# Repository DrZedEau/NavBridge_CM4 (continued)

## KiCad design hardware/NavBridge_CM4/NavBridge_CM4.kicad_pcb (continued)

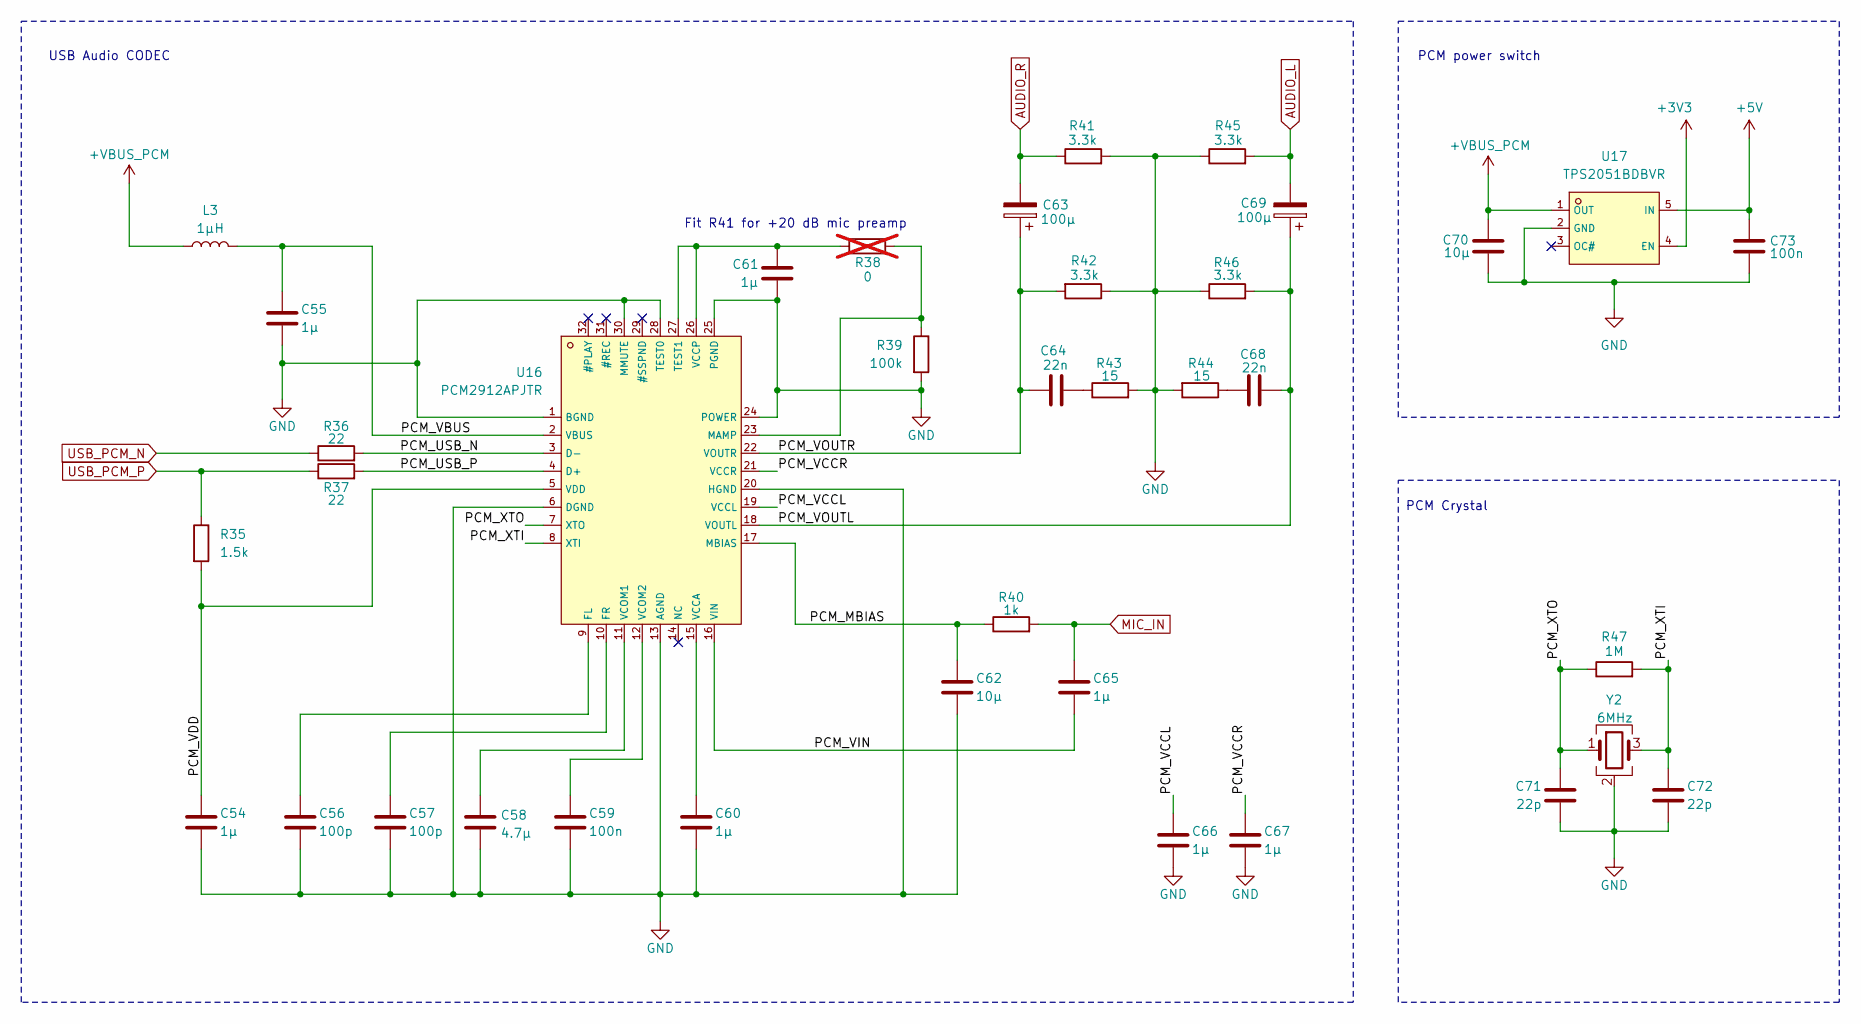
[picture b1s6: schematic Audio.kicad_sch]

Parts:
C54, C55, C60, C61, C65, C66, C67: 1µ; C_0402_1005Metric; LCSC C52923
C56, C57: 100p; C_0402_1005Metric; LCSC C1546
C58: 4.7µ; C_0402_1005Metric; LCSC C23733
C59, C73: 100n; C_0402_1005Metric; LCSC C307331
C62: 10µ; C_0603_1608Metric; LCSC C96446
C63, C69: 100µ; CP_EIA-3528-21_Kemet-B; LCSC C16133
C64, C68: 22n; C_0402_1005Metric; LCSC C1532
C70: 10µ; C_0805_2012Metric; LCSC C15850
C71, C72: 22p; C_0402_1005Metric; LCSC C1555
L3: 1µH; L_1008_2520Metric; LCSC C435392
R35: 1.5k; R_0402_1005Metric; LCSC C25867
R36, R37: 22; R_0402_1005Metric; LCSC C25092
R38: 0; R_0603_1608Metric; LCSC C17168; not fitted
R39: 100k; R_0402_1005Metric; LCSC C25741
R40: 1k; R_0402_1005Metric; LCSC C11702
R41, R42, R45, R46: 3.3k; R_0402_1005Metric; LCSC C25890
R43, R44: 15; R_0603_1608Metric; LCSC C22810
R47: 1M; R_0402_1005Metric; LCSC C26083
U16: PCM2912APJTR; C475497_TQFP-32_L7_0-W7_0-P0_80-LS9_0-TL; LCSC C475497
U17: TPS2051BDBVR; C24593_SOT-23-5_L3_0-W1_7-P0_95-LS2_8-BR; LCSC C24593
Y2: 6MHz; Crystal_SMD_FOX_FQ7050-4Pin_7.0x5.0mm; LCSC C179631

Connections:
+3V3: U17.4 (EN); also elsewhere on the board
+5V: C73.1, U17.5 (IN); also elsewhere on the board
+VBUS_PCM: C70.2, L3.1, U17.1 (OUT)
/Audio/PCM_MBIAS: C62.1, R40.1, U16.17 (MBIAS)
/Audio/PCM_USB_N: R36.2, U16.3 (D-)
/Audio/PCM_USB_P: R37.2, U16.4 (D+)
/Audio/PCM_VBUS: C55.1, L3.2, U16.2 (VBUS)
/Audio/PCM_VCCL: C66.1, U16.19 (VCCL)
/Audio/PCM_VCCR: C67.1, U16.21 (VCCR)
/Audio/PCM_VDD: C54.1, R35.2, U16.5 (VDD)
/Audio/PCM_VIN: C65.2, U16.16 (VIN)
/Audio/PCM_VOUTL: C68.1, C69.1, R46.2, U16.18 (VOUTL)
/Audio/PCM_VOUTR: C63.1, C64.1, R42.2, U16.22 (VOUTR)
/Audio/PCM_XTI: C72.1, R47.2, U16.8 (XTI), Y2.3
/Audio/PCM_XTO: C71.1, R47.1, U16.7 (XTO), Y2.1
AUDIO_L: C69.2, R45.2; also elsewhere on the board
AUDIO_R: C63.2, R41.1; also elsewhere on the board
GND: C54.2, C55.2, C56.2, C57.2, C58.2, C59.2, C60.2, C61.2, C62.2, C66.2, C67.2, C70.1, C71.2, C72.2, C73.2, R39.2, R41.2, R42.1, R43.2, R44.2, R45.1, R46.1, U16.1 (BGND), U16.6 (DGND), U16.13 (AGND), U16.20 (HGND), U16.24 (POWER), U16.25 (PGND), U16.28 (TEST0), U16.30 (MMUTE), U17.2 (GND), Y2.2 (G), Y2.4 (G); also elsewhere on the board
MIC_IN: C65.1, R40.2; also elsewhere on the board
unnamed: C64.2, R43.1
unnamed: C68.2, R44.1
unnamed: C56.1, U16.9 (FL)
unnamed: C57.1, U16.10 (FR)
unnamed: R38.2, R39.1, U16.23 (MAMP)
unnamed: C61.1, R38.1, U16.26 (VCCP), U16.27 (TEST1)
unnamed: C60.1, U16.15 (VCCA)
unnamed: C58.1, U16.11 (VCOM1)
unnamed: C59.1, U16.12 (VCOM2)
USB_PCM_N: R36.1; also elsewhere on the board
USB_PCM_P: R35.1, R37.1; also elsewhere on the board

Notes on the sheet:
PCM Crystal
Fit R41 for +20 dB mic preamp
USB Audio CODEC
PCM power switch

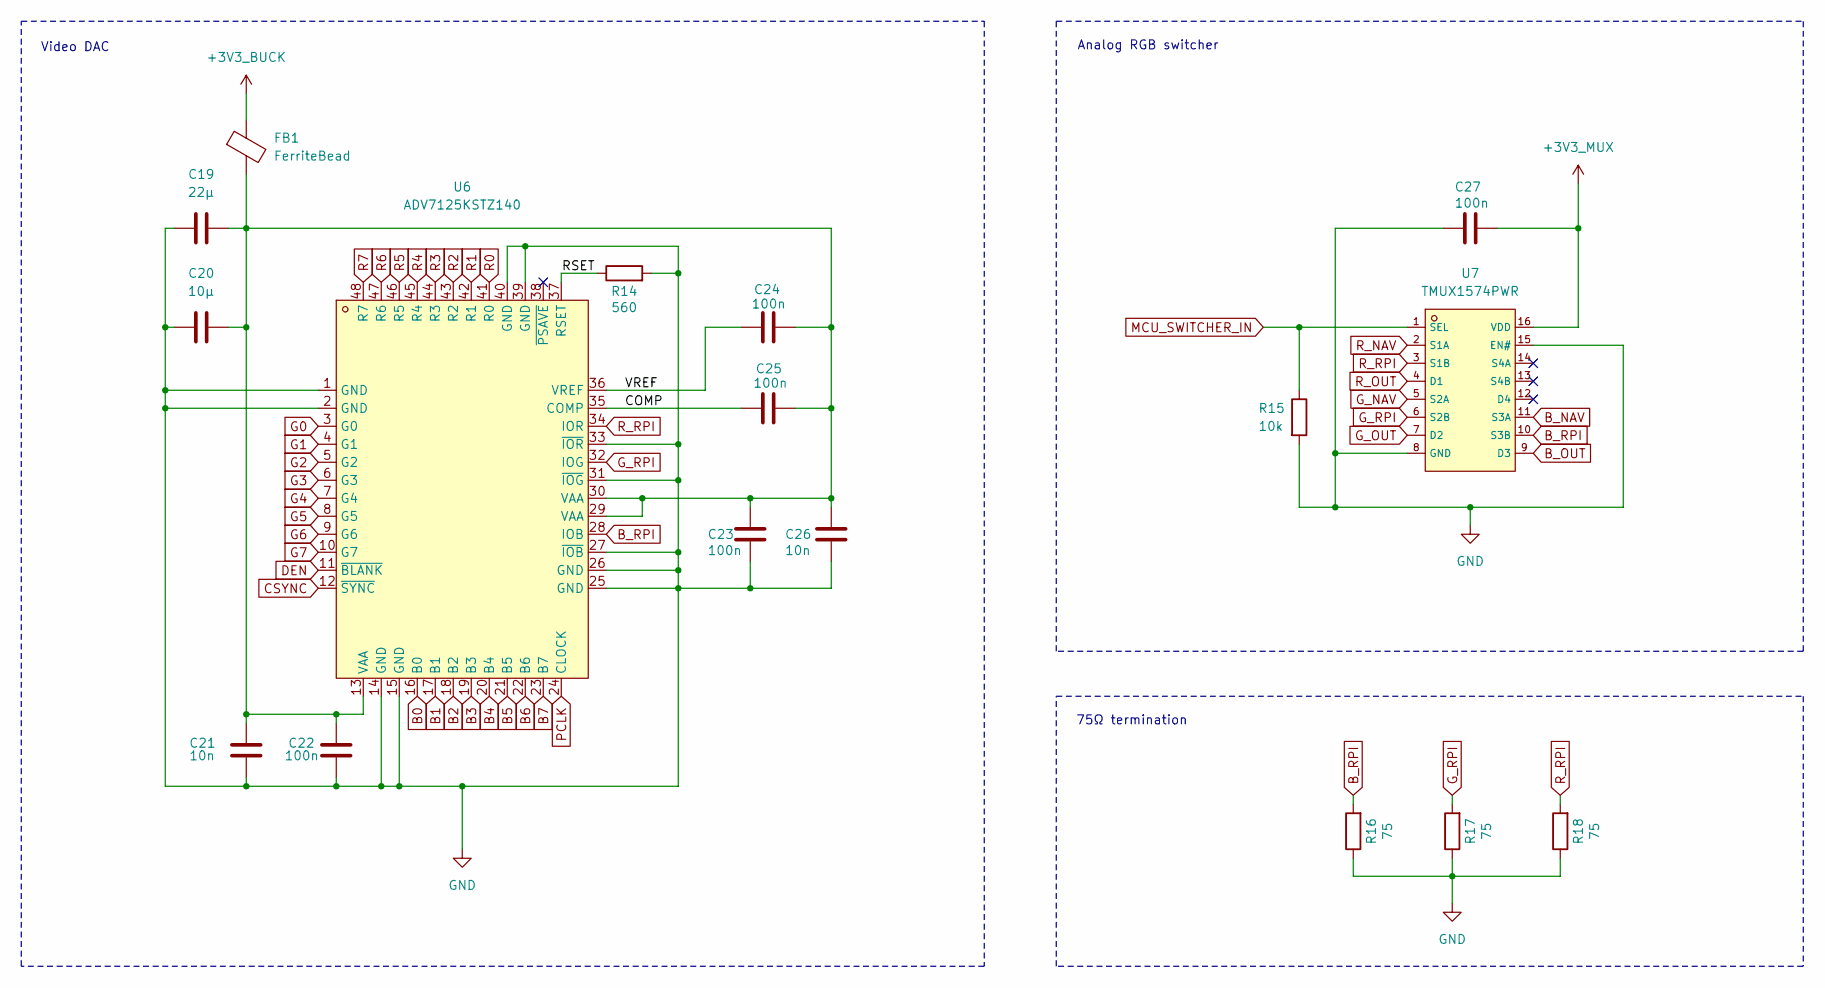
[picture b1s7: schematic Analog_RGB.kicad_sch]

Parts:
C19: 22µ; C_0805_2012Metric; LCSC C45783
C20: 10µ; C_0603_1608Metric; LCSC C19702
C21, C26: 10n; C_0402_1005Metric; LCSC C15195
C22, C23, C24, C25, C27: 100n; C_0402_1005Metric; LCSC C307331
FB1: FerriteBead; R_0603_1608Metric; LCSC C14709
R14: 560; R_0603_1608Metric; LCSC C23204
R15: 10k; R_0402_1005Metric; LCSC C25744
R16, R17, R18: 75; R_0402_1005Metric; LCSC C25133
U6: ADV7125KSTZ140; LQFP-48_L7.0-W7.0-P0.50-LS9.0-BL; LCSC Part C9668
U7: TMUX1574PWR; C2673443_TSSOP-16_L5_0-W4_4-P0_65-LS6_4-BL; LCSC C2673443

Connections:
+3V3_BUCK: FB1.1; also elsewhere on the board
+3V3_MUX: C27.2, U7.16 (VDD); also elsewhere on the board
/Analog_RGB/COMP: C25.2, U6.35 (COMP)
/Analog_RGB/RSET: R14.1, U6.37 (RSET)
/Analog_RGB/VREF: C24.2, U6.36 (VREF)
B0: U6.16 (B0); also elsewhere on the board
B1: U6.17 (B1); also elsewhere on the board
B2: U6.18 (B2); also elsewhere on the board
B3: U6.19 (B3); also elsewhere on the board
B4: U6.20 (B4); also elsewhere on the board
B5: U6.21 (B5); also elsewhere on the board
B6: U6.22 (B6); also elsewhere on the board
B7: U6.23 (B7); also elsewhere on the board
B_NAV: U7.11 (S3A); also elsewhere on the board
B_OUT: U7.9 (D3); also elsewhere on the board
B_RPI: R16.2, U6.28 (IOB), U7.10 (S3B)
CSYNC: U6.12 (~SYNC); also elsewhere on the board
DEN: U6.11 (~BLANK); also elsewhere on the board
G0: U6.3 (G0); also elsewhere on the board
G1: U6.4 (G1); also elsewhere on the board
G2: U6.5 (G2); also elsewhere on the board
G3: U6.6 (G3); also elsewhere on the board
G4: U6.7 (G4); also elsewhere on the board
G5: U6.8 (G5); also elsewhere on the board
G6: U6.9 (G6); also elsewhere on the board
G7: U6.10 (G7); also elsewhere on the board
GND: C19.1, C20.1, C21.1, C22.1, C23.1, C26.1, C27.1, R14.2, R15.2, R16.1, R17.1, R18.1, U6.1 (GND), U6.2 (GND), U6.14 (GND), U6.15 (GND), U6.25 (GND), U6.26 (GND), U6.27 (~IOB), U6.31 (~IOG), U6.33 (~IOR), U6.39 (GND), U6.40 (GND), U7.8 (GND), U7.15 (EN#); also elsewhere on the board
G_NAV: U7.5 (S2A); also elsewhere on the board
G_OUT: U7.7 (D2); also elsewhere on the board
G_RPI: R17.2, U6.32 (IOG), U7.6 (S2B)
MCU_SWITCHER_IN: R15.1, U7.1 (SEL); also elsewhere on the board
unnamed: C19.2, C20.2, C21.2, C22.2, C23.2, C24.1, C25.1, C26.2, FB1.2, U6.13 (VAA), U6.29 (VAA), U6.30 (VAA)
PCLK: U6.24 (CLOCK); also elsewhere on the board
R0: U6.41 (R0); also elsewhere on the board
R1: U6.42 (R1); also elsewhere on the board
R2: U6.43 (R2); also elsewhere on the board
R3: U6.44 (R3); also elsewhere on the board
R4: U6.45 (R4); also elsewhere on the board
R5: U6.46 (R5); also elsewhere on the board
R6: U6.47 (R6); also elsewhere on the board
R7: U6.48 (R7); also elsewhere on the board
R_NAV: U7.2 (S1A); also elsewhere on the board
R_OUT: U7.4 (D1); also elsewhere on the board
R_RPI: R18.2, U6.34 (IOR), U7.3 (S1B)

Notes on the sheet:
Video DAC
Analog RGB switcher
75Ω termination

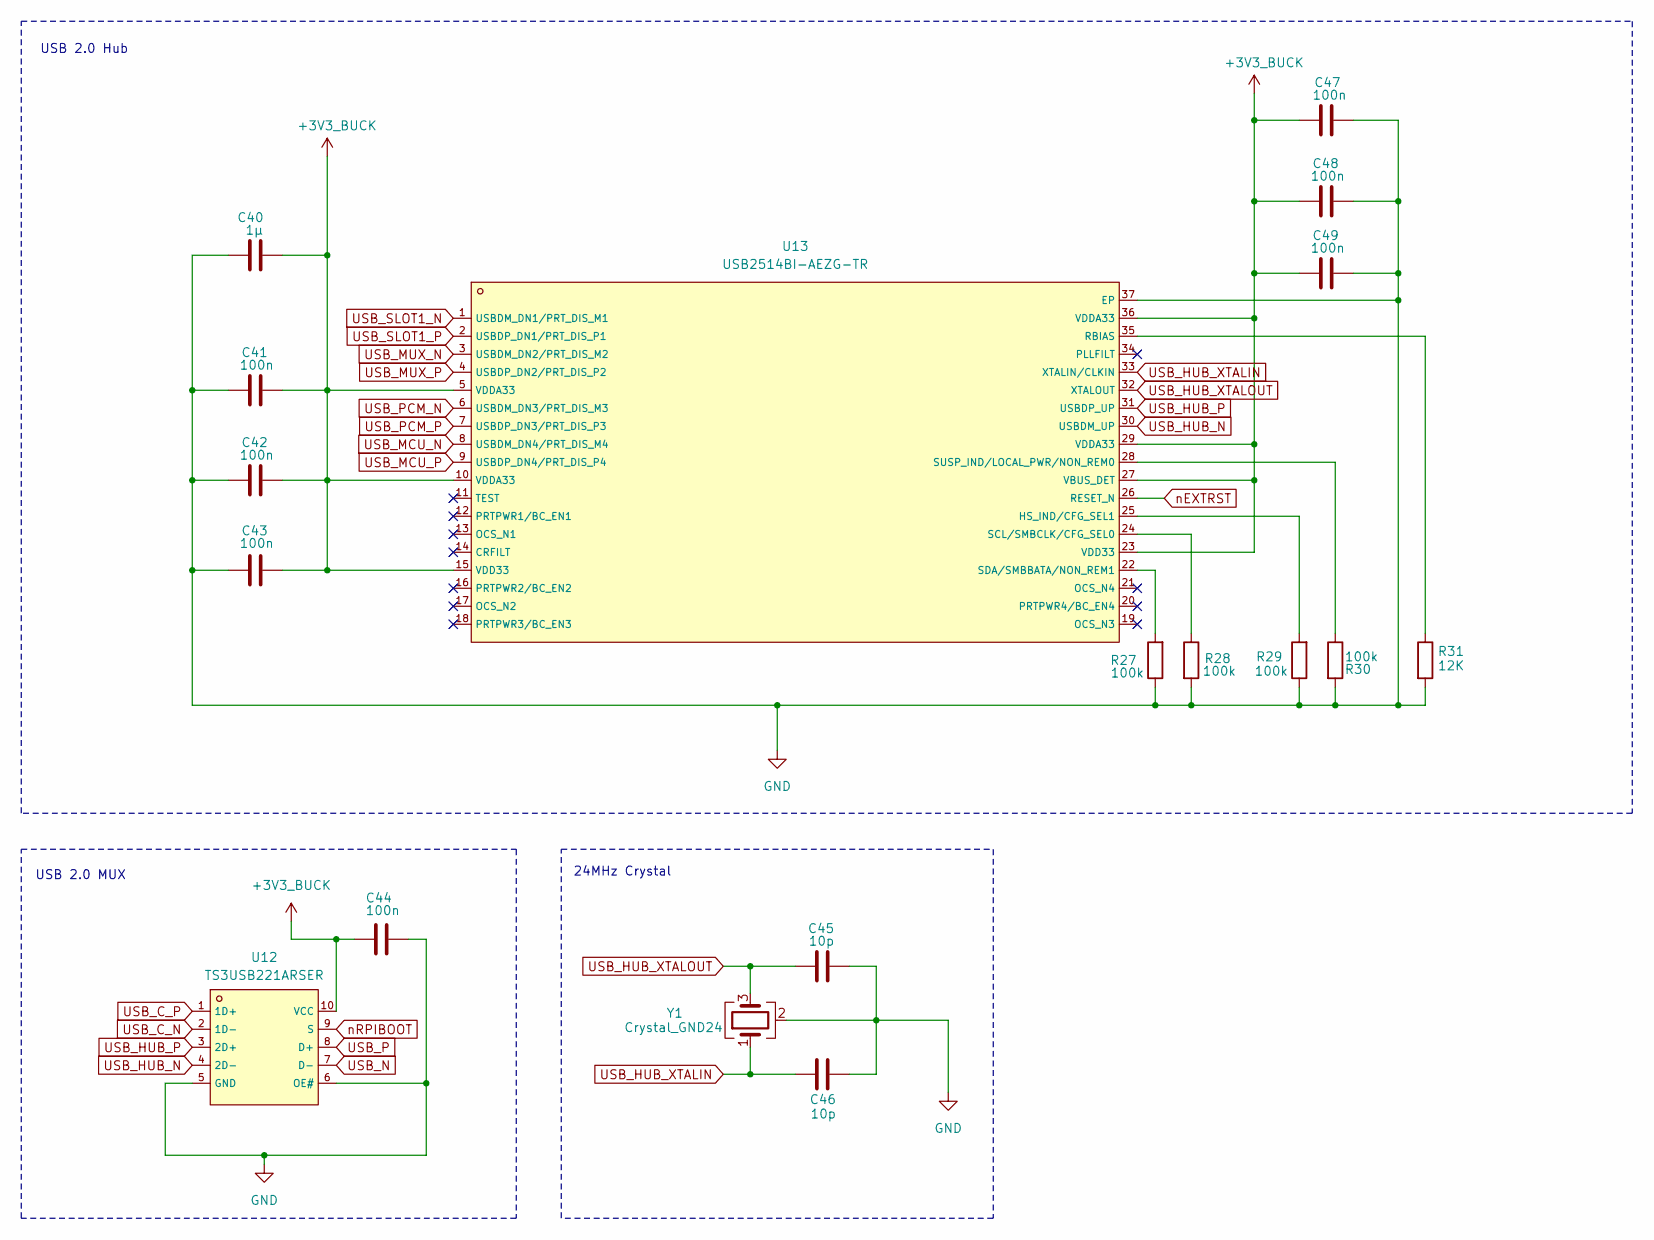
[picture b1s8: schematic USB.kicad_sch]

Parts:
C40: 1µ; C_0402_1005Metric; LCSC C52923
C41, C42, C43, C44, C47, C48, C49: 100n; C_0402_1005Metric; LCSC C307331
C45, C46: 10p; C_0402_1005Metric; LCSC C32949
R27, R28, R29, R30: 100k; R_0402_1005Metric; LCSC C25741
R31: 12K; R_0402_1005Metric; LCSC C25752
U12: TS3USB221ARSER; C128396_UQFN-10_L2_0-W1_5-P0_50-BL; LCSC C128396
U13: USB2514BI-AEZG-TR; C58940_TQFN-36_L6_0-W6_0-P0_50-BL-EP3_7; LCSC C58940
Y1: Crystal_GND24; Crystal_SMD_2016-4Pin_2.0x1.6mm; LCSC C6616880

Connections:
+3V3_BUCK: C40.2, C41.2, C42.2, C43.2, C44.1, C47.1, C48.1, C49.1, U12.10 (VCC), U13.5 (VDDA33), U13.10 (VDDA33), U13.15 (VDD33), U13.23 (VDD33), U13.27 (VBUS_DET), U13.29 (VDDA33), U13.36 (VDDA33); also elsewhere on the board
GND: C40.1, C41.1, C42.1, C43.1, C44.2, C45.2, C46.2, C47.2, C48.2, C49.2, R27.1, R28.2, R29.1, R30.2, R31.2, U12.5 (GND), U12.6 (OE#), U13.37 (EP), Y1.2 (G), Y1.4 (G); also elsewhere on the board
unnamed: R29.2, U13.25 (HS_IND/CFG_SEL1)
unnamed: R31.1, U13.35 (RBIAS)
unnamed: R28.1, U13.24 (SCL/SMBCLK/CFG_SEL0)
unnamed: R27.2, U13.22 (SDA/SMBBATA/NON_REM1)
unnamed: R30.1, U13.28 (SUSP_IND/LOCAL_PWR/NON_REM0)
USB_C_N: U12.2 (1D-); also elsewhere on the board
USB_C_P: U12.1 (1D+); also elsewhere on the board
USB_HUB_N: U12.4 (2D-), U13.30 (USBDM_UP)
USB_HUB_P: U12.3 (2D+), U13.31 (USBDP_UP)
USB_HUB_XTALIN: C46.1, U13.33 (XTALIN/CLKIN), Y1.1
USB_HUB_XTALOUT: C45.1, U13.32 (XTALOUT), Y1.3
USB_MCU_N: U13.8 (USBDM_DN4/PRT_DIS_M4); also elsewhere on the board
USB_MCU_P: U13.9 (USBDP_DN4/PRT_DIS_P4); also elsewhere on the board
USB_MUX_N: U13.3 (USBDM_DN2/PRT_DIS_M2); also elsewhere on the board
USB_MUX_P: U13.4 (USBDP_DN2/PRT_DIS_P2); also elsewhere on the board
USB_N: U12.7 (D-); also elsewhere on the board
USB_P: U12.8 (D+); also elsewhere on the board
USB_PCM_N: U13.6 (USBDM_DN3/PRT_DIS_M3); also elsewhere on the board
USB_PCM_P: U13.7 (USBDP_DN3/PRT_DIS_P3); also elsewhere on the board
USB_SLOT1_N: U13.1 (USBDM_DN1/PRT_DIS_M1); also elsewhere on the board
USB_SLOT1_P: U13.2 (USBDP_DN1/PRT_DIS_P1); also elsewhere on the board
nEXTRST: U13.26 (RESET_N); also elsewhere on the board
nRPIBOOT: U12.9 (S); also elsewhere on the board

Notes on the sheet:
USB 2.0 Hub
24MHz Crystal
USB 2.0 MUX

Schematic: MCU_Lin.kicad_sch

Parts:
C28, C30, C31, C34, C35, C37, C38, C39: 100n; C_0402_1005Metric; LCSC C307331
C29, C36: 4.7µ; C_0402_1005Metric; LCSC C23733
C32: 10µ; C_1206_3216Metric; LCSC C13585
C33: 4.7µ; C_0805_2012Metric; LCSC C1779
CN5: 20021521-00010C1LF; C598547_IDC-SMD_10P-P1_27_X1270WVS-2X05B-6TV01; LCSC C598547
D5, D7: 1N4148W; D_SOD-123; LCSC C81598
D6: LED_Y; LED_0603_1608Metric; LCSC C89811
R19, R23: 10k; R_0402_1005Metric; LCSC C25744
R20, R21, R22: 1k; R_0402_1005Metric; LCSC C11702
R24: 1k; R_1206_3216Metric; LCSC C4410
R25: 150k; R_0402_1005Metric; LCSC C25755
R26: 100k; R_0402_1005Metric; LCSC C25741
SW2, SW3: SW_Push; SW_SPST_TS-1088-xR020; LCSC C720477
U8, U10: ATA663231-GBQW; C5225740_DFN-8_L3_0-W3_0-P0_65-BL-EP-1; LCSC C5225740
U9: STM32C071KBTx; LQFP-32_7x7mm_P0.8mm; LCSC C42116633
U11: TPS2117DRLR; C22399676_SOT-583-8_L2_1-W1_2-P0_50-LS1_6-BL; LCSC Part C22399676

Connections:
+3V3: C39.1, CN5.1, R22.1, SW3.2, U11.6 (VIN2); also elsewhere on the board
+3V3_LIN_REG: C29.1, C30.2, C35.2, R25.1, U8.8 (VCC), U11.3 (VIN1), U11.5 (MODE)
+3V3_MUX: C33.1, C34.1, U9.4 (VDD), U11.2 (VOUT), U11.7 (VOUT); also elsewhere on the board
+3V3_SENSE: R22.2, U9.10 (PA3)
+BATT: D5.2 (A), D7.2 (A); also elsewhere on the board
CSYNC: U9.19 (PA9); also elsewhere on the board
GND: C28.1, C29.2, C30.1, C31.1, C32.2, C33.2, C34.2, C35.1, C36.2, C37.2, C38.1, C39.2, CN5.3, CN5.5, CN5.9, D6.1 (K), R19.2, R23.2, R26.2, SW2.1, U8.5 (GND), U8.9 (EP), U9.5 (VSS), U10.5 (GND), U10.9 (EP), U11.1 (GND); also elsewhere on the board
HSYNC: U9.18 (PA8); also elsewhere on the board
IBUS_CAR: U8.6 (LIN); also elsewhere on the board
IBUS_NAV: R24.1, U10.6 (LIN); also elsewhere on the board
MCU_BUCK_EN: U9.9 (PA2); also elsewhere on the board
MCU_LIN1_EN: R19.1, U8.2 (EN), U9.29 (PB5)
MCU_LIN1_RX: U8.1 (RXD), U9.31 (PB7)
MCU_LIN1_TX: U8.4 (TXD), U9.30 (PB6)
MCU_LIN2_EN: R23.1, U9.28 (PB4), U10.2 (EN)
MCU_LIN2_RX: U9.12 (PA5), U10.1 (RXD)
MCU_LIN2_TX: U9.11 (PA4), U10.4 (TXD)
MCU_SWITCHER_IN: U9.21 (PA10); also elsewhere on the board
NRST: C28.2, CN5.10, SW2.2, U9.6 (PF2)
unnamed: D6.2 (A), R20.2
unnamed: D7.1 (K), R24.2
unnamed: R21.1, SW3.1
unnamed: R20.1, U9.8 (PA1)
unnamed: C36.1, C37.1, U10.8 (VCC)
unnamed: R25.2, R26.1, U11.4 (PR1)
SWCLK: CN5.4, R21.2, U9.25 (PA14)
SWDIO: CN5.2, U9.24 (PA13)
USB_MCU_N: U9.22 (PA11); also elsewhere on the board
USB_MCU_P: U9.23 (PA12); also elsewhere on the board
VS: C31.2, C32.1, C38.2, D5.1 (K), U8.7 (VS), U10.7 (VS)
VSYNC: U9.13 (PA6); also elsewhere on the board

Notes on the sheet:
MCU
MCU Power MUX
SWD Header
LIN Nav side
LIN Car side

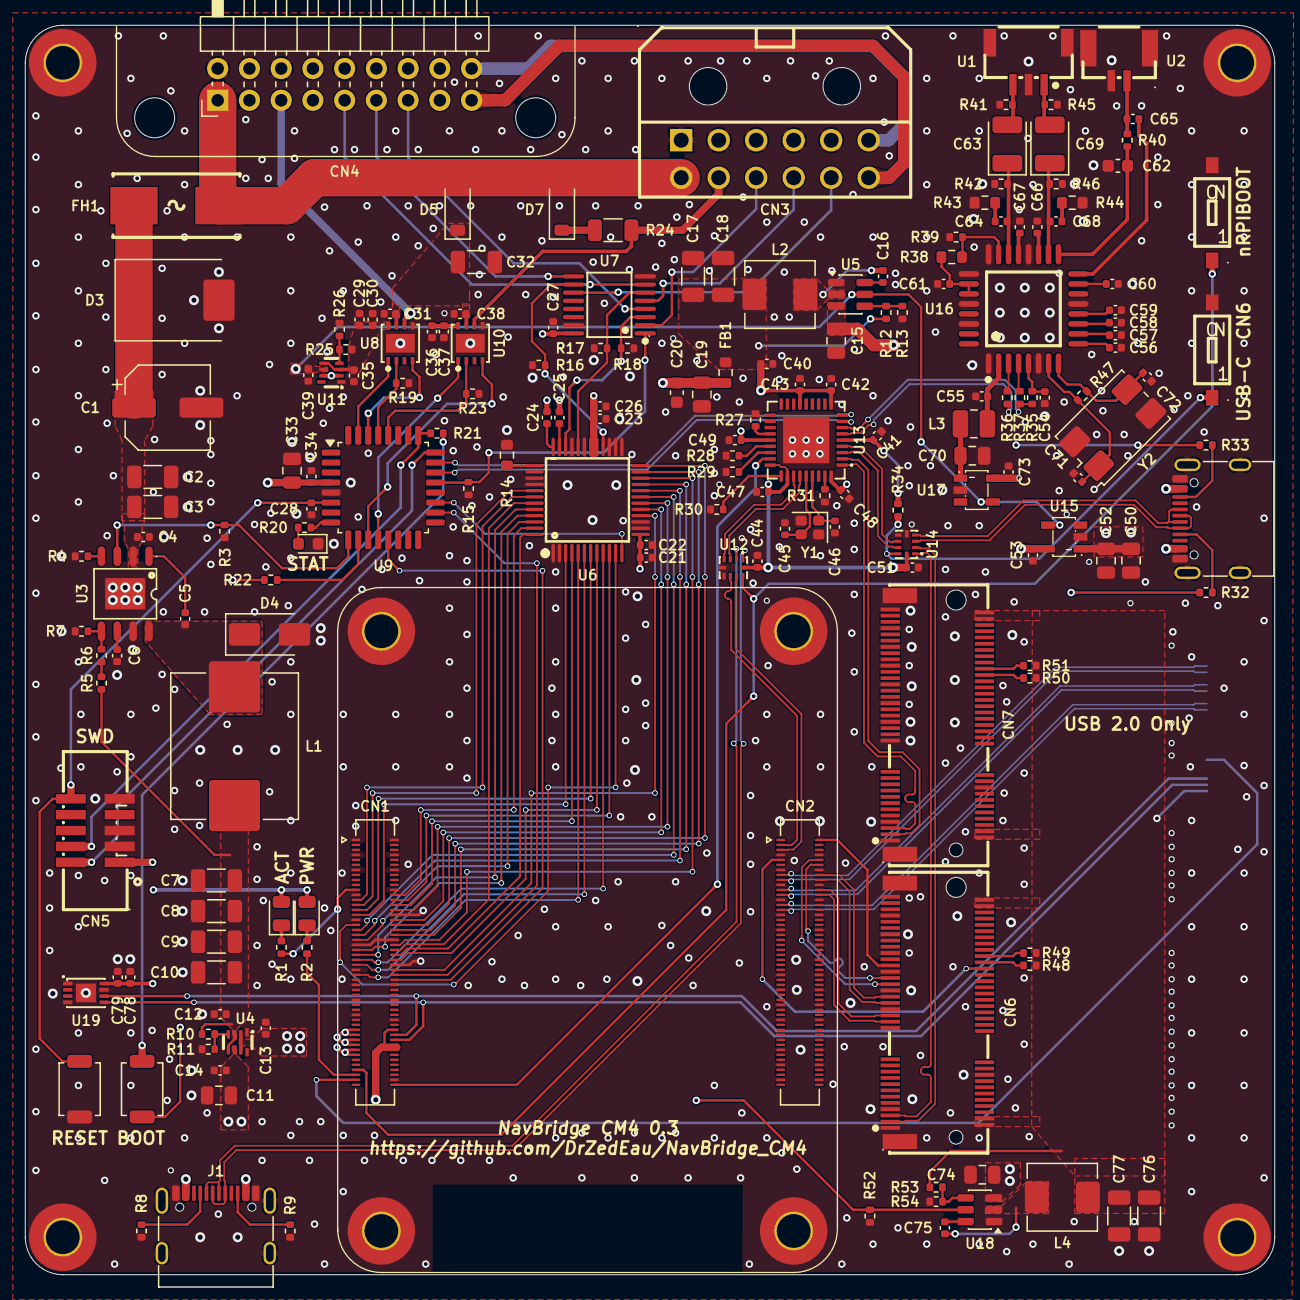
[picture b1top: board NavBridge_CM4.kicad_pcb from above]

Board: 4 copper layers, 100.0 x 100.0 mm, 189 parts (1 on the bottom side), 172 nets.

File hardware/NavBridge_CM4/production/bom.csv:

Designator,Footprint,Quantity,Value,LCSC Part #
C1,CP_Elec_6.3x5.8,1,100µ,C128464
"C10, C7, C8, C9",1206,4,47µ,C96123
"C11, C33, C50",0805,3,4.7µ,C1779
"C12, C13, C14, C16, C22, C23, C24, C25, C27, C28, C30, C31, C34, C35, C37, C38, C39, C4, C41, C42, C43, C44, C47, C48, C49, C5, C51, C53, C59, C6, C73, C75, C79",0402,33,100n,C307331
"C15, C52, C70, C74",0805,4,10µ,C15850
"C17, C18, C76, C77",1206,4,22µ,C12891
C19,0805,1,22µ,C45783
"C2, C3",1206,2,4.7µ,C29823
C20,0603,1,10µ,C19702
"C21, C26",0402,2,10n,C15195
"C29, C36, C58",0402,3,4.7µ,C23733
C32,1206,1,10µ,C13585
"C40, C54, C55, C60, C61, C65, C66, C67, C78",0402,9,1µ,C52923
"C45, C46",0402,2,10p,C32949
"C56, C57",0402,2,100p,C1546
C62,0603,1,10µ,C96446
"C63, C69",CP_EIA-3528-21_Kemet-B,2,100µ,C16133
"C64, C68",0402,2,22n,C1532
"C71, C72",0402,2,22p,C1555
"CN1, CN2",Hirose_DF40C-100DS-0.4V_2x50_P0.4mm,2,DF40C-100DS-0.4V,C597931
CN3,C277636_CONN-TH_12P-P3_00-S3_00_L12_2-W21_7-EH10_7,1,Molex 430451200,C277636
CN4,PinHeader_2x09_P2.54mm_Horizontal,1,X1313 Car connector,C492437
CN5,C598547_IDC-SMD_10P-P1_27_X1270WVS-2X05B-6TV01,1,20021521-00010C1LF,C598547
"CN6, CN7",C2977809_PCIE-SMD_2199230-4,2,2199230-4_C2977809,C2977809
D1,0805,1,LED_G,C2297
D2,0805,1,LED_R,C84256
D3,D_SMC,1,SMCJ24A,C19077604
D4,D_SMA,1,SS54,C22452
"D5, D7",D_SOD-123,2,1N4148W,C81598
D6,0603,1,LED_Y,C89811
FB1,0603,1,FerriteBead,C14709
FH1,C108518_FUSE-SMD_L9_8-W5_0_01550900M,1,01550900M,C108518
"J1, J2",USB_C_Receptacle_G-Switch_GT-USB-7010ASV,2,USB_C_Receptacle_USB2.0_16P,C2988369
L1,L_Sunlord_MWSA1003S,1,6.8uH,C2453947
"L2, L4",L_Sunlord_MWSA0518S,2,6.8uH,C2928918
L3,1008,1,1µH,C435392
"R1, R2, R20, R21, R22, R40",0402,6,1k,C11702
R10,0402,1,330k,C25778
"R11, R12, R26, R27, R28, R29, R30, R39, R5, R53",0402,10,100k,C25741
"R13, R54",0402,2,22k,C25768
R14,0603,1,560,C23204
"R15, R19, R23, R3, R34, R48, R49, R50, R51, R52",0402,10,10k,C25744
"R16, R17, R18",0402,3,75,C25133
R24,1206,1,1k,C4410
R25,0402,1,150k,C25755
R31,0402,1,12K,C25752
"R32, R33",0402,2,56k,C25796
R35,0402,1,1.5k,C25867
"R36, R37",0402,2,22,C25092
R4,0402,1,49.9k,C25897
"R41, R42, R45, R46",0402,4,3.3k,C25890
"R43, R44",0603,2,15,C22810
R47,0402,1,1M,C26083
"R6, R8, R9",0402,3,5.1k,C25905
R7,0402,1,18k,C25762
"SW1, SW4",C3312309_SW-SMD_NIDEC_CHS-01B1,2,CHS-01B1,C3312309
"SW2, SW3",SW_SPST_TS-1088-xR020,2,SW_Push,C720477
U1,C514175_CONN-TH_SM03B-GHS-TB-LF-SN,1,SM03B-GHS,C514175
"U10, U8",C5225740_DFN-8_L3_0-W3_0-P0_65-BL-EP-1,2,ATA663231-GBQW,C5225740
"U11, U4",C22399676_SOT-583-8_L2_1-W1_2-P0_50-LS1_6-BL,2,TPS2117DRLR,C22399676
"U12, U14",C128396_UQFN-10_L2_0-W1_5-P0_50-BL,2,TS3USB221ARSER,C128396
U13,C58940_TQFN-36_L6_0-W6_0-P0_50-BL-EP3_7,1,USB2514BI-AEZG-TR,C58940
"U15, U17",C24593_SOT-23-5_L3_0-W1_7-P0_95-LS2_8-BR,2,TPS2051BDBVR,C24593
U16,C475497_TQFP-32_L7_0-W7_0-P0_80-LS9_0-TL,1,PCM2912APJTR,C475497
"U18, U5",SOT-23-6,2,TPS54202DDC,C191884
U19,C33770534_DFN-8_L3_0-W2_0-P0_50-BL-EP1_6,1,MFI343S00177-L,C33770534
U2,C189893_CONN-SMD_SM02B-GHS-TB-LF-SN,1,SM02B-GHS,C189893
U20,C5468341_FPC-SMD_22P-P0_50_0524352271,1,0524352271,C5468341
U3,C485817_SO-8_L4_9-W3_9-P1_27-LS6_0-BL-EP,1,LMR14030SQDDARQ1,C485817
U6,LQFP-48_L7.0-W7.0-P0.50-LS9.0-BL,1,ADV7125KSTZ140,C9668
U7,C2673443_TSSOP-16_L5_0-W4_4-P0_65-LS6_4-BL,1,TMUX1574PWR,C2673443
U9,LQFP-32_7x7mm_P0.8mm,1,STM32C071KBTx,C42116633
Y1,Crystal_SMD_2016-4Pin_2.0x1.6mm,1,Crystal_GND24,C6616880
Y2,Crystal_SMD_FOX_FQ7050-4Pin_7.0x5.0mm,1,6MHz,C179631

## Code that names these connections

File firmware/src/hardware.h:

/* SPDX-License-Identifier: GPL-2.0-only
 *
 * Board I/O of the NavBridge CM4 (schematic sheet MCU_Lin, U9 = STM32C071KBT6):
 *
 *   PA1  (8)   STAT LED D6, active high                    always on
 *   PA2  (9)   MCU_BUCK_EN, LMR14030 5 V buck enable       10k pull-down, off at power-on
 *   PA3  (10)  +3V3_SENSE, CM 3.3 V rail through 1k        high while the CM is on
 *   PA4  (11)  MCU_LIN2_TX  USART2_TX AF1  -> U10 (navigation I-Bus)
 *   PA5  (12)  MCU_LIN2_RX  USART2_RX AF1  <- U10
 *   PA6  (13)  VSYNC        EXTI6          <- CM DPI
 *   PA8  (18)  HSYNC        TIM1_CH1 AF2   <- CM DPI
 *   PA9  (19)  CSYNC        TIM1_CH2 AF2   -> ADV7125 SYNC
 *   PA10 (21)  MCU_SWITCHER_IN, TMUX1574 SEL: low = factory navigation, high = Raspberry Pi
 *   PA11/PA12  USB D-/D+ to the USB2514B hub
 *   PA13/PA14  SWD; PA14 is also BOOT0 (BOOT button SW3 to 3.3 V through 1k)
 *   PB4  (28)  MCU_LIN2_EN, U10 EN (10k pull-down)
 *   PB5  (29)  MCU_LIN1_EN, U8 EN (10k pull-down)
 *   PB6  (30)  MCU_LIN1_TX  USART1_TX AF0  -> U8 (car I-Bus)
 *   PB7  (31)  MCU_LIN1_RX  USART1_RX AF0  <- U8
 */
#ifndef HARDWARE_H
#define HARDWARE_H

#include <stdint.h>

#define LED_PIN       1u   /* GPIOA */
#define BUCK_EN_PIN   2u   /* GPIOA */
#define SENSE_3V3_PIN 3u   /* GPIOA */
#define RGB_SEL_PIN   10u  /* GPIOA */
#define BOOT0_PIN     14u  /* GPIOA */
#define LIN2_EN_PIN   4u   /* GPIOB */
#define LIN1_EN_PIN   5u   /* GPIOB */

typedef enum {
    RGB_NAV = 0,  /* factory navigation picture (TMUX1574 SEL low) */
    RGB_RPI = 1,  /* Raspberry Pi picture through the ADV7125 */
} rgb_source_t;

/* On the reset clock, before anything else: LED on, buck back on if it was on before a warm
 * reset (the Raspberry Pi may be running from it), RGB switch on the navigation picture. */
void hw_early_init(void);


void hw_set_led(int on);
void hw_set_buck(int on);
int hw_buck_on(void);

void hw_set_rgb(rgb_source_t source);
rgb_source_t hw_rgb(void);

int hw_cm_3v3_present(void);  /* raw +3V3_SENSE level */

void hw_set_lin_enable(int on);  /* both ATA663231, normal mode when on */
int hw_lin_enabled(void);        /* EN still driven high from before a jump */

/* BOOT button (SW3) held at RESET. */
int hw_boot_button_held(void);

/* Before the firmware jumps to the bootloader: pins the bootloader does not use in a quiet
 * state (LIN TX recessive, navigation picture on screen, CSYNC released). */
void hw_prepare_bootloader(void);

#endif
